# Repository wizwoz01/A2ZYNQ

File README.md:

# A2ZYNQ

**One Apple II slot, seven peripheral cards, running on a Smart Zynq SP.**

A2ZYNQ is my port of the [A2FPGA](https://github.com/a2fpga/a2fpga_core)
Multicard core to the **Smart Zynq SP**, a small Xilinx Zynq-7020 board with
a dual-core ARM, DDR3, HDMI, Ethernet and an SD card slot. A hand-wired proto
card sits in an Apple II slot and connects the Apple bus to the Zynq with a
pair of ribbon cables. The FPGA side runs the A2FPGA core (the same one the
A2N20v2 card uses) and answers for every empty slot in the machine. The ARM
side runs Linux and a small service program, `a2hostd`, that serves disk
images from the SD card, does the networking and runs the boot menu.

The end result: I boot my **Apple IIe** (plain NMOS 6502, 64K, 40
columns) into a disk menu, pick a game from a folder on an SD card, swap disks
with a button on the board, play Total Replay off a 32 MB hard disk, hear the
Mockingboard over HDMI, put the IIe on my home network, and drag disk images
onto it from my PC over FTP. One card does all of it.

```
 Apple IIe slot                          Smart Zynq SP
+--------------------+   2x 40-pin    +-----------------------------------------+
|  proto card        |   ribbons      |  PL (FPGA)                PS (ARM)      |
|  5x SN74LVC245A    |===============>|  A2FPGA core      SPI     Linux         |
|  6x NPN open-coll. |<===============|  - Disk II        over    a2hostd       |
|  /RES sense        |   + ground     |  - ProDOS HDD     AXI <=> - disk images |
+--------------------+   bundle       |  - SSC, Uthernet          - disk menu   |
                                      |  - Mockingboard           - FTP, telnet |
                                      |  - SuperSprite            - SSC bridge  |
                                      |  - HDMI video/audio       - Ethernet    |
                                      +-----------------------------------------+
                                           |HDMI          |SD card   |Ethernet
```

## See it running

All of these are straight HDMI captures from the board on my IIe. The two
GIFs run at double speed. (The row of numbers along the top is the debug
line; DIP switch 4 hides it.)

**The disk menu follows the card.** Same card, moved through slots 1 to 7.
In slots 1-3 the menu says `SLOT n MENU` and the Disk II answers in slot 6;
in slots 4-7 it becomes that slot's own `DISK MENU`.

**Booting a game from the menu.** Arrow down to Oregon Trail, `RETURN`, and
the IIe boots it off the image on the SD card.

**The card test disk.** ProDOS boots, then the test program
([tests/cardtest](tests/cardtest)) goes through every virtual card in
slots 2-7, writes an 8 KB file back to the floppy, reads it back, and ends
with `0 FAILED`. This one is a video with sound, so you can hear the
Mockingboard and SuperSprite test tones come out of the HDMI. Turn the sound up.

https://github.com/user-attachments/assets/9a4790e4-1fdd-43f0-96c2-07918a6907ac

## Why I built this

I wanted an A2FPGA for my IIe, and I already had a Smart Zynq SP on my bench.
The A2N20v2-Enhanced design pairs a Gowin FPGA with a BL616 microcontroller
that serves disks, runs the menu and bridges the network. The Zynq has both
halves on one chip: a decent FPGA, and ARM cores that can run real Linux. So
instead of building another card, I ported the Enhanced design over. The FPGA
logic stays the A2FPGA core, and the BL616's job moves to a Linux program
that speaks the same SPI protocol the BL616 did.

It turned into a much longer project than I expected. The core had to come
off Gowin primitives and onto Xilinx ones, the SDRAM had to become Zynq DDR,
and the Apple bus turned out to be a lot less forgiving than the datasheets
make it look. Along the way I found and fixed a stack of things: an SPI bit
race, a Disk II write path that stored every nibble twice, a hard disk read
that could return stale data, a video shadow that painted neighbour bytes, and
one level translator chip that simply can't do this job (more on that below).
It all works now on my IIe, and the card test disk in this repo passes every
slot.

## What the card provides

With the card in slot 1 (how I run it):

| Slot | Card | What you get |
|------|------|--------------|
| 1 | *(the physical card)* | nothing virtual here, the IIe powers up to BASIC |
| 2 | Super Serial Card | a 6551 serial port, bridged to **TCP port 6551** on the board, so the Apple's serial port shows up on your network |
| 3 | Uthernet II (W5100) | Ethernet for IP65 programs; Apple frames go straight out the board's Ethernet port, and the Apple gets its own address from your router |
| 4 | Mockingboard | two AY-3-8910 sound chips + 6522 VIAs, stereo over HDMI |
| 5 | ProDOS hard disk | two drives up to 32 MB each (`hdd1.hdv`, `hdd2.po`), bootable with `PR#5` |
| 6 | Disk II + disk menu | two 5.25" drives fed from disk images on the SD card, with a boot menu, read **and** write |
| 7 | SuperSprite | TMS9918A video chip with sprites, mixed over the Apple picture on HDMI, plus an AY sound chip |

The Disk II follows the card: put the card in slot 6 and the Disk II answers
in slot 6 and boots at power-up, the hard disk moves to slot 5. Slots 2, 3, 4
and 7 never move. The full table is in the
[board README](boards/a2n20v2-SmartZynq/README.md#slot-map).

Plus:

- **HDMI out** with the Apple picture regenerated (text, lores, hires; the
  core also does 80 columns and double hires, which I can't test without an
  80-column card), with the Apple speaker, Mockingboard and SuperSprite sound
  all on the HDMI audio.
- **A disk menu that runs on the Apple itself.** Folders, arrow keys,
  jump by first letter, `RETURN` boots, `TAB` puts a disk in drive 2, `ESC`
  drops you at BASIC. It remembers the last disk you booted.
- **Disk swapping with board buttons.** `KEY1` on the Smart Zynq puts the next
  disk of a set into drive 1 (`ultima31.dsk` -> `ultima32.dsk`), `KEY2` the
  previous one. A line under the Apple picture on HDMI tells you what's in
  the drive. No keyboard hotkey, nothing a game can trip over.
- **Writes are saved.** DOS 3.3 `SAVE`, ProDOS files, game saves: changed
  tracks are written back into the image on the SD card.
- **FTP server** on the board, so copying games over is drag and drop from
  Windows Explorer, FileZilla or `curl`.
- **Telnet console** with `status`, `rescan` and an FPGA dump command.
- **A card test disk** ([tests/cardtest](tests/cardtest)) that exercises
  every virtual card from the Apple side and writes a log back to the disk.

## Status

This is a working hobby build, not a product. What I've tested on my own
unenhanced IIe:

| | |
|--|--|
| Disk II boot, menu, folders, ESC, drive 2 | works |
| Floppy writes (DOS 3.3 and ProDOS) | works, verified with the card test (0 failed) |
| Multi-disk swap with KEY1/KEY2 | works |
| ProDOS hard disk read/write, Total Replay | works |
| Mockingboard, SuperSprite | works (card test tones and green box) |
| Uthernet II with IP65 (DHCP, DATE65, HFS65 web server) | works |
| Super Serial Card registers | works (card test) |
| SSC over the network (TCP 6551) | works in simulation, real-Apple test still on my list |
| Apple IIgs, enhanced IIe, II+ | not tested. The IIgs signals (M2SEL, M2B0) are wired on the card, but I've never tried it. IIgs mode is off by default because DIP switch 4 hides the HDMI debug numbers instead (one setting in `top.sv` swaps it back) |
| Powering the board from the Apple's +5V | not done yet, see [the power notes](boards/a2n20v2-SmartZynq/docs/power.md) first |
| The rev 1.0 PCB | ordered, waiting on the boards; see [Work in progress](#work-in-progress) |

Known limits on an unenhanced IIe (these are the machine, not the card):
anything built for the 65C02 (ProDOS 8 2.x, Contiki, the C versions of the
IP65 apps) locks up, and 80-column programs show every second character
without an 80-column card.

The open items are in [boards/a2n20v2-SmartZynq/TODO.md](boards/a2n20v2-SmartZynq/TODO.md).

## Work in progress

The firmware, the gateware and the hand-wired card all work today. The
hardware is where most of the open work is, so here's where things stand
and what I'm planning next.

### The PCB (rev 1.0, waiting on boards)

The red proto card works, but it's an evening of point-to-point wiring and
two ribbon cables hanging out of the Apple. So I laid out a real card:
[hardware/pcb](hardware/pcb). Same circuit, same five SN74LVC245A, on an
Apple II card outline (tebl's compact prototyping card), and the Smart Zynq
plugs straight onto it with its HDMI and Ethernet facing the back of the
Apple. No ribbons, no hand wiring.

Where it's at:

- [x] Layout done, KiCad DRC clean, every pad checked against the netlist
      CSVs in [hardware/](hardware/).
- [x] Gerbers, BOM and an assembly sheet in [hardware/pcb](hardware/pcb).
- [x] Boards ordered from the fab.
- [ ] **Waiting on delivery.** Nothing below this line has happened yet.
- [ ] Assemble the first card, do the meter checks from the PCB README
      before it goes anywhere near the IIe.
- [ ] Bring-up in the Apple: card test disk, Disk II boot, hard disk,
      Mockingboard, Uthernet, all the things the proto card already passes.
- [ ] Check the fit: header stack height, standoffs, clearance between the
      Smart Zynq's through-hole pins and the transistors underneath, and
      whether the card clears its neighbours in the slots.
- [ ] Fix whatever rev 1.0 gets wrong and post a rev 1.1 with photos.

**Until I've built one and it passes, treat rev 1.0 as untested.** If you
want to build something right now, build the proto card; the wiring notes
are complete and that's the version I've been running for weeks.

### Other things I'm working toward

- **Powering the Smart Zynq from the Apple.** The PCB has an optional
  Schottky diode and jumper (D1, JP1) to feed the board from the Apple's
  +5V. It ships open and stays that way until I've measured the current
  draw on USB and tried it on the bench. Notes in
  [power.md](boards/a2n20v2-SmartZynq/docs/power.md).
- **SSC network bridge on the real Apple.** It passes in simulation; the
  real IIe test is next on my list.
- **Other machines.** Enhanced IIe, II+, and the IIgs (the IIgs signals are
  already on the card). I only own an unenhanced IIe, so reports are
  welcome.
- **A prebuilt release** (bitstream, `a2hostd`, and maybe a ready SD
  image) so you don't need Vivado to try it.
- **A small web page on the board** for uploading disks and changing
  settings, instead of FTP and editing `settings.ini`.
- **`.woz` image support** for copy-protected originals.
- **Locking down the network side.** FTP, telnet and the serial bridge have
  no passwords right now. Fine on my home network, not fine anywhere else.
  Don't put the board on a network you don't trust yet.
- **Recovering a crashed 6502** from the board, which needs a closer look at
  the /RES and /INH stages.

The full list with the details is in
[TODO.md](boards/a2n20v2-SmartZynq/TODO.md). If you build one, I'd love to
hear how it went, especially on a machine I haven't tried.

## What you need

- An Apple II with a free slot. Mine is a IIe.
- A **Smart Zynq SP** board (XC7Z020-1CLG484) and a USB-C cable/charger for it.
- The **red proto card**, hand-wired per [hardware/RED_PROTO_CARD_WIRING.md](hardware/RED_PROTO_CARD_WIRING.md):
  five SN74LVC245A, seven 2N3904s, a few resistors, two 2x20 headers and two
  40-pin ribbon cables. Parts list in [hardware/BOM.csv](hardware/BOM.csv).
  **Use real SN74LVC245A for the data bus.** Auto-direction translators
  (TXB0108, TXS0108E) do not work, I tried both.
  (Or the [PCB version](hardware/pcb) once I've confirmed it works, see
  [Work in progress](#work-in-progress).)
- A microSD card (4 GB or bigger) for Linux and your disk images.
- An HDMI monitor, and an Ethernet cable if you want FTP and networking.
- To build from source: a Linux PC with **Vivado 2024.2** (the free
  Standard edition covers the XC7Z020) and an ARM cross compiler.

## Getting started

1. **Build or grab the bitstream.** [docs/BUILDING.md](docs/BUILDING.md)
   walks through it: download the Xillinux kit into `third_party/`, run one
   Vivado script, wait half an hour.
2. **Make the SD card.** [docs/INSTALLING.md](docs/INSTALLING.md) covers
   writing Xillinux, putting the bitstream, device tree and `a2hostd` on it,
   and updating a running board later over the network.
3. **Wire the proto card**, check it with a meter before anything goes near
   the Apple, and plug it in with everything powered off.
4. **Power up**: board first (USB-C), wait about 40 seconds, then the Apple.
5. **Use it**: [docs/USER_GUIDE.md](docs/USER_GUIDE.md) explains every card
   with examples you can type in.

## Repository layout

This follows the same layout as `a2fpga_core`, so anyone who knows the
upstream tree will find their way around.

```
A2ZYNQ/
  README.md            you are here
  LICENSE              layered license (MIT + GPL parts), same terms as A2FPGA
  LICENSES/            full GPL-2.0 and GPL-3.0 texts
  hdl/                 the A2FPGA core, with my fixes (disk, hdd, video, ssc bridge...)
  boards/
    a2n20v2-SmartZynq/ everything specific to the Smart Zynq SP
      README.md        the board guide: slots, menu, images, FTP, troubleshooting
      TODO.md          what's left
      hdl/             the a2n20v2-Enhanced top level and SPI connector, ported
      rtl/             Smart Zynq wrapper: board top, bus PHY, clocking, DDR, SPI master
      vivado/          build.tcl, rebuild.tcl, sources.tcl, constraints, BD patch
      device_tree/     merged Xillinux device tree with the A2 UIO node
      src/a2hostd/     the Linux service (C++14): disks, menu, network, SSC bridge
      src/systemd/     a2hostd.service
      tools/           SD card writer, a2hostd cross build, device tree merge
      docs/            how the Zynq side works: SPI map, storage, power, lessons
  docs/
    USER_GUIDE.md      how to use every card, with examples
    BUILDING.md        building the bitstream and a2hostd
    INSTALLING.md      SD card, first boot, updating
    core/              A2FPGA core documentation (from upstream, with my notes)
    images/            HDMI captures used in this README
  hardware/            proto card wiring, BOM, pin maps, schematic (PDF)
    pcb/               the card as a PCB: KiCad board, Gerbers, BOM (rev 1.0, untested)
  tests/
    bus_timing/        xsim testbenches for the bus, Disk II, HDD, menu, SSC bridge...
    cardtest/          Apple II test program for slots 2-7 (cc65)
    menu6502/          runs the disk menu code on a 6502 emulator
  tools/               serial console and file transfer helpers, ProDOS disk builder
  third_party/         where the Xillinux kit goes (not included, see its README)
```

## How it differs from a2n20v2-Enhanced

If you know the upstream board, here's the short version of what changed:

- **BL616 -> Linux.** `a2hostd` on the Zynq ARM takes over everything the
  BL616 firmware did. It talks to the FPGA with the same SPI protocol, through
  a small AXI SPI master in the PL that Linux drives through UIO, so the
  core's `bl616_spi_connector` barely had to change.
- **SDRAM -> DDR3.** The core's memory clients share an arbiter that is
  bridged across clock domains into the Zynq's HP2 AXI port, using a reserved
  8 MiB window at `0x1E000000`.
- **Gowin -> Xilinx.** Clocking (MMCM), HDMI TMDS serializers (OSERDESE2),
  tri-states and a few memories were rewritten or wrapped for Vivado.
- **CPLD -> five 245s.** The original card captures the bus with a CPLD; the
  proto card uses five SN74LVC245A and puts all the capture and timing logic
  in the FPGA, with drive timing you can tune from Linux.
- **Storage paths I added.** Floppy saves read the track straight back out of
  the drive's nibble memory, and hard disk blocks go straight to and from the
  controller's sector buffer. The upstream SDRAM round trip wasn't reliable on
  this port (the card test caught it).
- **Extras:** the 6502 disk menu with folders and ESC, the Disk II following
  the card's slot, board-button disk swaps with an HDMI notice line, the SSC
  network bridge, FTP/telnet on the board, and BRAM shadows for text and
  hires video.

## Things I learned the hard way

- **Auto-direction level shifters don't belong on the Apple data bus.**
  TXB0108 and TXS0108E both read isolated 0 bits as 1 (things like `$BD`
  became `$FF` 40-85% of the time) and no amount of FPGA timing fixed it. An
  SN74LVC245A with the FPGA driving DIR and OE# fixed it on the first boot.
- **6502 dummy reads are real bus cycles.** `STA abs,X`, `STA (zp),Y` and
  Applesoft's `POKE` all read the address before they write it. Any register
  with a read side effect (auto-increment, clear-on-read) gets hit twice. The
  Uthernet II DHCP bug I chased was exactly this.
- **Act at the end of the bus cycle.** The card sees selects at the start of
  PHI0, so anything that "fires on select" can fire twice per access. That's
  what made the Disk II write every nibble twice.
- **Don't restart the host service under a running Apple.** If `a2hostd`
  drops out, the card stops answering and the 6502 crashes. Restart it only
  with the Apple switched off.

The long version, with the measurements, is in
[boards/a2n20v2-SmartZynq/docs/lessons-learned.md](boards/a2n20v2-SmartZynq/docs/lessons-learned.md).

## Documentation

| Document | What's in it |
|----------|--------------|
| [boards/a2n20v2-SmartZynq/README.md](boards/a2n20v2-SmartZynq/README.md) | The board guide: slot map, disk images, first boot, menu, FTP, network, troubleshooting |
| [docs/USER_GUIDE.md](docs/USER_GUIDE.md) | Every card explained with examples (BASIC listings, PC commands) |
| [docs/BUILDING.md](docs/BUILDING.md) | Building the bitstream and `a2hostd`, running the tests |
| [docs/INSTALLING.md](docs/INSTALLING.md) | SD card, first boot, updating the board |
| [boards/a2n20v2-SmartZynq/docs/](boards/a2n20v2-SmartZynq/docs/) | How the Zynq port works inside: SPI host interface, storage, SSC bridge, power, lessons learned |
| [hardware/RED_PROTO_CARD_WIRING.md](hardware/RED_PROTO_CARD_WIRING.md) | Wiring the proto card, the electrical rules, bring-up checks |
| [hardware/pcb/README.md](hardware/pcb/README.md) | The PCB version: ordering, how the Smart Zynq sits on it, assembly and meter checks |
| [docs/core/](docs/core/) | The A2FPGA core docs: architecture, bus interface, memory, video, audio, peripheral cards |

## Credits

This project stands on other people's work, and I want to be clear about that.

- **[A2FPGA](https://github.com/a2fpga/a2fpga_core)** by Ed Anuff and the
  A2FPGA contributors. The core, the virtual cards, the video pipeline and the
  a2n20v2-Enhanced design I ported all come from there. My port started from
  upstream commit `f97dc342`.
- The open cores inside A2FPGA: the 6522 VIA by Gideon Zweijtzer
  (1541ultimate), the IIR filter by Sorgelig (MiSTer), the F18A/TMS9918 core,
  the YM2149 (AY-3-8910) and 6551 cores, the TMS5220, and the AppleWin team, whose HDD
  firmware and 6-and-2 GCR code live on in the hard disk ROM and in `a2hostd`.
- **[Xillybus](https://xillybus.com)** for Xillinux and the Smart Zynq SP
  demo bundle that the build starts from.
- **[Total Replay](https://github.com/a2-4am/4cade)** by 4am and qkumba, which
  is what I keep on hard disk 1.
- **[IP65](https://github.com/cc65/ip65)** for the Uthernet test disk.
- **[cc65](https://cc65.github.io)** for building the card test, and
  **[py65](https://github.com/mnaberez/py65)** for testing the menu code
  without an Apple.

## License

Same terms as A2FPGA: MIT for the A2FPGA and A2ZYNQ files, with a few GPL
components that make the bitstream as a whole GPL-3.0. Details in
[LICENSE](LICENSE). The Xillinux kit is Xillybus's and is not included.

Apple, Apple II and ProDOS are trademarks of Apple Inc. This is a hobby
project with no connection to Apple, AMD/Xilinx, Xillybus or the Smart Zynq
maker.

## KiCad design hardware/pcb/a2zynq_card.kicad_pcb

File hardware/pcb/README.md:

# pcb: the A2ZYNQ slot card

This is the red proto card turned into a real PCB. The circuit is exactly the
one in [../RED_PROTO_CARD_WIRING.md](../RED_PROTO_CARD_WIRING.md) and the
`../*.csv` netlists (five SN74LVC245A, Q1-Q7, the 5 V sense divider, SW1),
and the Smart Zynq SP plugs straight onto the card, so there are no ribbon
cables and no hand wiring.

> **Status: rev 1.0, boards ordered, not built yet.** The board passes KiCad's DRC with no
> errors, and I checked every pad against the CSV netlists. The first
> boards have not been through the Apple yet, so treat rev 1.0 as a
> prototype: order the minimum quantity and do the meter checks below before
> it goes near the IIe.

## Order it

Upload **`a2zynq_card_gerbers.zip`** to the fab (JLCPCB, PCBWay, OSH Park...).

| Setting | Value |
|---------|-------|
| Layers | 2 |
| Size | 99.7 x 78.7 mm (68.6 mm above the edge fingers) |
| Thickness | 1.6 mm (the Apple slot wants 1.57 mm / 0.062") |
| Copper | 1 oz |
| Smallest track / gap | 0.25 mm / 0.2 mm |
| Smallest hole | 0.3 mm (vias) |
| Surface finish | ENIG, or "gold fingers" if the fab offers it |
| Edge fingers | bevel (chamfer) the finger edge if offered; it makes insertion kinder to the slot |

The outline and the 50 edge fingers follow tebl's
[Apple ][ Prototyping Card](https://github.com/tebl/Apple2-Prototyping-Card)
(the compact one): same size, same finger position and pitch, so it sits in
the slot exactly like that card.

## How the Smart Zynq sits on it

- The Smart Zynq goes **component side up**, turned so its **HDMI and
  Ethernet face the back panel** of the Apple (the right-hand end of the card,
  looking at the component side with the fingers down). Its USB-C ports face
  the keyboard.
- **JZ1 = Smart Zynq U12** (bank 33, the header on the HDMI side of the
  Smart Zynq). It's the row next to the edge fingers.
- **JZ2 = Smart Zynq U13** (bank 35, the header on the Ethernet side). It's
  the row along the top edge.
- Pin 1 of both is the **square pad at the right-hand end**. Pins 35/36 are
  ground, 37/38 are 3.3 V, 39/40 are the board's 5 V, the same as on the
  Smart Zynq.
- The four M3 holes line up with the Smart Zynq's four corner holes. Use
  standoffs the same height as the header stack (about 11 mm with ordinary
  8.5 mm female headers on the card and the Smart Zynq's pins underneath).

Header and hole positions come from the board maker's dimension drawing
(`Smart_ZYNQ_SP_V1_SIZE_20230502.pdf`): header pins start 23.94 mm from the
board edge, the two pin-1 rows are 48.08 mm apart, holes 87.14 x 45 mm. Which
header is U12 comes from the Smart Zynq schematic and its ball map (bank 33
is the top half of the BGA, next to the HDMI header).

If your Smart Zynq has its header pins on the top side (they point up, for
ribbon cables), you can still use the card: fit **2x20 box headers** in JZ1
and JZ2 and run two short ribbon cables, U12 to JZ1 and U13 to JZ2, pin 1 to
pin 1. The numbering on the card is the same either way.

### Height under the Smart Zynq

Everything on the card except SW1, D1, JP1, R23 and TP1 sits under the
Smart Zynq, so keep it low:

- solder the '245s straight in or use low-profile sockets,
- push the transistors down to about 5 mm above the board,
- C6 and C7 must be **7 mm tall or less** (low-profile electrolytics).

The Smart Zynq's Ethernet jack is through-hole, and its pins come out of the
underside right above Q1-Q6, the same way the HDMI shell legs sit above Q7
and R13-R18. Before tightening the standoffs, put the board on and look along
the gap from the side: nothing on the card should touch the pins.

The Smart Zynq's microSD socket isn't on its top side (it's not on the
maker's top-view drawing), so expect to lift the board off the sockets to
swap cards. I update the card over the network anyway (see the board
README).

## Parts

Full list: [a2zynq_card_bom.csv](a2zynq_card_bom.csv). The "old schematic name"
column ties each part back to the hand-wired card and the PDF schematic
(RBASE1, ROE_IN, CDEC3 and so on).

The resistors use the small **0204 size** (3.6 mm body, 5.08 mm lead
spacing), for example Vishay SFR16S or Yageo MFR-12. The usual 1/4 W
6.3 mm resistors don't fit the footprint. Everything else is ordinary
through-hole.

Differences from the hand-wired card:

- U5 is an **SN74LVC245A** with DIR and OE# from the FPGA, as in the wiring
  notes. The old PDF schematic still shows the TXB0108; ignore that page.
- No separate ground bundle: both headers carry two ground pins each, and
  the card has ground pours on both sides. TP1 is a ground loop for a scope
  clip.
- U13 pin 27 (`pl_ready`) isn't connected to anything, same as before.

## SW1

Left-hand end of the card, next to the fingers, so it's reachable with the
Smart Zynq in place. Positions 1-4 left to right are the same as always:
1 scanlines, 2 Apple speaker on HDMI, 3 Power-on-Reset hold, 4 hide the HDMI
debug numbers (see the board README). Each switch pulls its JZ2 pin
(15-18) to ground.

## The 5 V link (JP1 and D1, optional)

Leave **JP1 open** and the card is "ground only", exactly like the wiring
notes: Apple +5V only feeds the 15k/22k sense divider and the Smart Zynq runs
from USB-C.

To run the Smart Zynq from the Apple's +5V, fit **D1 (1N5822, 3 A Schottky)
first**: it stands upright on the round pad with its band (cathode) at the
top, and the lead from the band goes down to the square pad marked K. Then
put a jumper on JP1. Apple slot pin 25 then goes through JP1 and D1 to the Smart
Zynq's 5 V (U13 pins 39/40) on a 1 mm track around the edge of the card, and
D1 stops USB power from back-feeding the Apple. Read
[docs/power.md](../../boards/a2n20v2-SmartZynq/docs/power.md) before doing
this: check the board's current on USB first, check 4.6 V or more at pin 39
under load, and keep DIP switch 3 ON.

## Before it goes in the Apple

1. Card alone, nothing fitted in the sockets yet: meter Apple finger 25 to
   26. It must not beep.
2. Fit the parts. Card alone again: finger 25 to 26 reads about 37k (the
   sense divider), not a short. Check every edge finger against its
   neighbours.
3. Smart Zynq on the card, card **not** in the Apple, board on USB-C: 3.3 V
   on pin 20 of each '245, and OE# (pin 19) high on all five. Without the
   Apple's 5 V the FPGA keeps the bus switched off, and the 10k pull-ups hold
   OE# high before the bitstream loads.
4. With the A2ZYNQ bitstream running and the card still out of the Apple,
   JZ2 pins 15-18 read 3.3 V with each switch OFF and 0 V with it ON.
5. Everything off. Card in the slot. Board first, then the Apple, and watch
   the `a2hostd` log for the detected slot.

Never plug or unplug the card (or the Smart Zynq) with either side powered.

## Files

| File | What it is |
|------|------------|
| `a2zynq_card_gerbers.zip` | Gerbers + drill files, ready to upload |
| `a2zynq_card.kicad_pcb`, `a2zynq_card.kicad_pro` | the board, opens in KiCad 9 |
| `a2zynq_card_bom.csv` | parts list |
| `top.png`, `bottom.png`, `assembly.pdf` | previews (the bottom one as seen from the back) and an assembly drawing |
| `drc.rpt` | KiCad's DRC report for the board: no errors, nothing unconnected; the warnings are silkscreen overlaps and the three footprints from my own library (JZ1, JZ2 and the edge fingers J1) |

There's no KiCad schematic for this board. The netlist is the `../*.csv`
files, and I checked every pad on the copper against them.

### Changing the board

Open `a2zynq_card.kicad_pro` in KiCad 9 and edit it in the PCB editor. Before
ordering, refill the zones (B) and run the DRC (Inspect > Design Rules
Checker). To make the fab zip the same way as the one here:

```bash
cd hardware/pcb
mkdir -p gerbers
kicad-cli pcb export gerbers --layers F.Cu,B.Cu,F.Mask,B.Mask,F.SilkS,B.SilkS,Edge.Cuts \
    --subtract-soldermask -o gerbers/ a2zynq_card.kicad_pcb
kicad-cli pcb export drill --format excellon --excellon-units mm --excellon-separate-th \
    -o gerbers/ a2zynq_card.kicad_pcb
rm -f a2zynq_card_gerbers.zip
(cd gerbers && zip -q -9 ../a2zynq_card_gerbers.zip *)
```

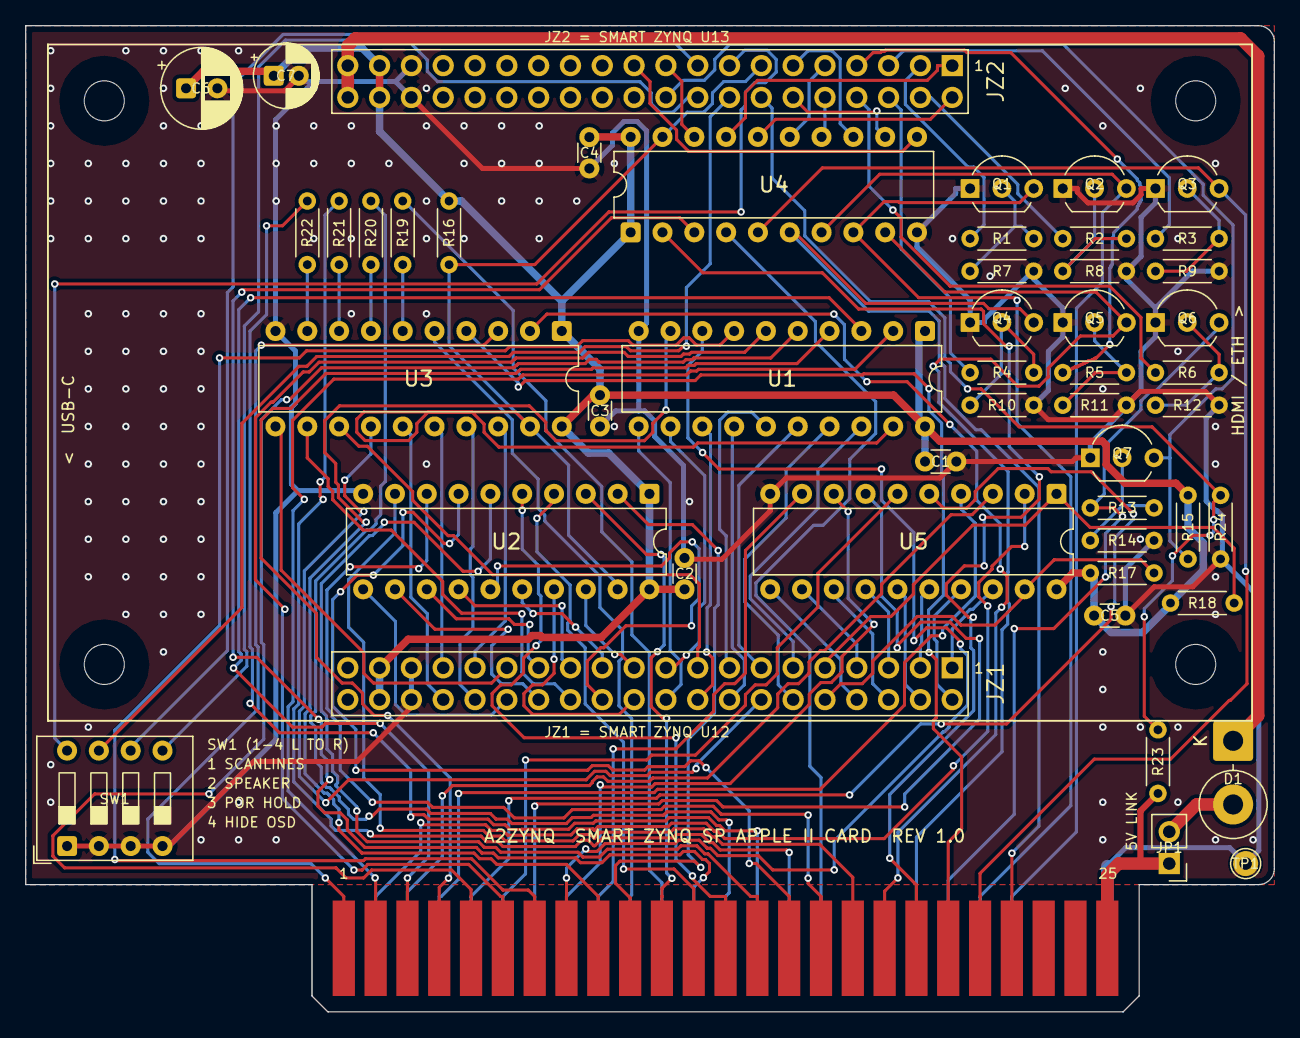
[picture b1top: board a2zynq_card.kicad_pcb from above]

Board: 2 copper layers, 99.7 x 78.7 mm, 54 parts (0 on the bottom side), 112 nets.

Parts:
C1, C2, C3, C4, C5: 100n; C_Disc_D3.0mm_W1.6mm_P2.50mm
C6: 100u; CP_Radial_D6.3mm_P2.50mm
C7: 10u; CP_Radial_D5.0mm_P2.00mm
D1: 1N5822 (option); D_DO-201AD_P5.08mm_Vertical_KathodeUp
J1: Apple II slot; Apple_II_Slot_Edge
JP1: 5V LINK (open); PinHeader_1x02_P2.54mm_Vertical
JZ1: Smart Zynq U12 (bank 33); SmartZynq_2x20_U12
JZ2: Smart Zynq U13 (bank 35); SmartZynq_2x20_U13
MH1, MH2, MH3, MH4: M3; MountingHole_3.2mm_M3
Q1, Q2, Q3, Q4, Q5, Q6, Q7: 2N3904; TO-92_Inline_Wide
R1, R2, R3, R4, R5, R6: 2.2k; R_Axial_DIN0204_L3.6mm_D1.6mm_P5.08mm_Horizontal
R7, R8, R9, R10, R11, R12, R16, R17, R18: 10k; R_Axial_DIN0204_L3.6mm_D1.6mm_P5.08mm_Horizontal
R13, R23: 15k; R_Axial_DIN0204_L3.6mm_D1.6mm_P5.08mm_Horizontal
R14: 100k; R_Axial_DIN0204_L3.6mm_D1.6mm_P5.08mm_Horizontal
R15: 4.7k; R_Axial_DIN0204_L3.6mm_D1.6mm_P5.08mm_Horizontal
R19, R20, R21, R22: 33R; R_Axial_DIN0204_L3.6mm_D1.6mm_P5.08mm_Horizontal
R24: 22k; R_Axial_DIN0204_L3.6mm_D1.6mm_P5.08mm_Horizontal
SW1: DIP x4; SW_DIP_SPSTx04_Slide_9.78x12.34mm_W7.62mm_P2.54mm
TP1: GND; TestPoint_THTPad_D2.0mm_Drill1.0mm
U1, U2, U3, U4, U5: SN74LVC245AN; DIP-20_W7.62mm

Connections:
5V_LINK: D1.2, JP1.2
A0: J1.2, U1.2
A1: J1.3, U1.3
A2: J1.4, U1.4
A2_5V_PRESENT: JZ2.14, R23.2, R24.1
A2_7M: JZ1.26, U3.12
A2_ADDR0: JZ1.11, U1.18
A2_ADDR1: JZ1.12, U1.17
A2_ADDR2: JZ1.13, U1.16
A2_ADDR3: JZ1.15, U1.15
A2_ADDR4: JZ1.16, U1.14
A2_ADDR5: JZ1.18, U1.13
A2_ADDR6: JZ1.19, U1.12
A2_ADDR7: JZ1.20, U1.11
A2_ADDR8: JZ1.21, U2.18
A2_ADDR9: JZ1.22, U2.17
A2_ADDR10: JZ1.23, U2.16
A2_ADDR11: JZ1.24, U2.15
A2_ADDR12: JZ1.25, U2.14
A2_ADDR13: JZ1.27, U2.13
A2_ADDR14: JZ1.28, U2.12
A2_ADDR15: JZ1.30, U2.11
A2_DATA0: JZ1.1, U5.18
A2_DATA1: JZ1.2, U5.17
A2_DATA2: JZ1.3, U5.16
A2_DATA3: JZ1.4, U5.15
A2_DATA4: JZ1.5, U5.14
A2_DATA5: JZ1.6, U5.13
A2_DATA6: JZ1.7, U5.12
A2_DATA7: JZ1.8, U5.11
A2_DATA_DIR: JZ1.9, R18.2, U5.1
A2_DATA_OE_N: JZ1.10, R17.2, U5.19
A2_DEVSEL_N: JZ1.34, U3.15
A2_DMA_ASSERT: JZ2.6, R4.1
A2_DMA_N_SENSE: JZ2.10, U4.14
A2_INH_ASSERT: JZ2.7, R5.1
A2_INH_N_SENSE: JZ2.21, U4.11
A2_IOSEL_N: JZ1.32, U3.17
A2_IOSTRB_N: JZ1.33, U3.16
A2_IRQ_ASSERT: JZ2.3, R1.1
A2_IRQ_N_SENSE: JZ2.12, U4.12
A2_M2B0: JZ2.2, U4.16
A2_M2SEL: JZ2.1, U4.17
A2_NMI_ASSERT: JZ2.4, R2.1
A2_NMI_N_SENSE: JZ2.11, U4.13
A2_PHI0: JZ1.14, U3.14
A2_PHI1: JZ1.17, U3.13
A2_Q3: JZ1.29, U3.11
A2_RDY_ASSERT: JZ2.5, R3.1
A2_RDY_N_SENSE: JZ2.9, U4.15
A2_RESET_ASSERT: JZ2.8, R6.1
A2_RESET_ASSERTED_SENSE: JZ2.20, Q7.3, R15.2
A2_RW: JZ1.31, U3.18
A2_SYNC: JZ2.19, U4.18
A3: J1.5, U1.5
A4: J1.6, U1.6
A5: J1.7, U1.7
A6: J1.8, U1.8
A7: J1.9, U1.9
A8: J1.10, U2.2
A9: J1.11, U2.3
A10: J1.12, U2.4
A11: J1.13, U2.5
A12: J1.14, U2.6
A13: J1.15, U2.7
A14: J1.16, U2.8
A15: J1.17, U2.9
BUS_INPUT_OE_N: JZ2.13, R16.2, U1.19, U2.19, U3.19, U4.19
CARD_5V: J1.25, JP1.1, R23.1
CLK7M: J1.36, R21.1
CLK7M_R: R21.2, U3.8
D0: J1.49, U5.2
D1: J1.48, U5.3
D2: J1.47, U5.4
D3: J1.46, U5.5
D4: J1.45, U5.6
D5: J1.44, U5.7
D6: J1.43, U5.8
D7: J1.42, U5.9
DEVSEL_N: J1.41, U3.5
DIP_SW1: JZ2.15, SW1.8
DIP_SW2: JZ2.16, SW1.7
DIP_SW3: JZ2.17, SW1.6
DIP_SW4: JZ2.18, SW1.5
DMA_N: J1.22, Q4.3, U4.6
GND: C1.2, C2.2, C3.2, C4.2, C5.2, C6.2, C7.2, J1.26, JZ1.35, JZ1.36, JZ2.35, JZ2.36, Q1.1, Q2.1, Q3.1, Q4.1, Q5.1, Q6.1, Q7.1, R7.2, R8.2, R9.2, R10.2, R11.2, R12.2, R14.2, R24.2, SW1.1, SW1.2, SW1.3, SW1.4, TP1.1, U1.10, U2.10, U3.10, U4.10, U5.10
INH_N: J1.32, Q5.3, U4.9
IOSEL_N: J1.1, U3.3
IOSTRB_N: J1.20, U3.4
IRQ_N: J1.30, Q1.3, U4.8
M2B0: J1.35, U4.4
M2SEL: J1.39, U4.3
NMI_N: J1.29, Q2.3, U4.7
PHI0: J1.40, R19.1
PHI0_R: R19.2, U3.6
PHI1: J1.38, R20.1
PHI1_R: R20.2, U3.7
Q1_BASE: Q1.2, R1.2, R7.1
Q2_BASE: Q2.2, R2.2, R8.1
Q3: J1.37, R22.1
Q3_BASE: Q3.2, R3.2, R9.1
Q3_R: R22.2, U3.9
Q4_BASE: Q4.2, R4.2, R10.1
Q5_BASE: Q5.2, R5.2, R11.1
Q6_BASE: Q6.2, R6.2, R12.1
Q7_BASE: Q7.2, R13.2, R14.1
RDY_N: J1.21, Q3.3, U4.5
RES_N: J1.31, Q6.3, R13.1
RW: J1.18, U3.2
SYNC: J1.19, U4.2
VCC3V3: C1.1, C2.1, C3.1, C4.1, C5.1, C6.1, C7.1, JZ1.37, JZ1.38, JZ2.37, JZ2.38, R15.1, R16.1, R17.1, R18.1, U1.1, U1.20, U2.1, U2.20, U3.1, U3.20, U4.1, U4.20, U5.20
ZYNQ_5V: D1.1, JZ2.39, JZ2.40

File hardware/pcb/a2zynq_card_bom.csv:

References,Qty,Value,Footprint,Old schematic name,Notes
C1 C2 C3 C4 C5,5,100 nF,C_Disc_D3.0mm_W1.6mm_P2.50mm,CDEC1 CDEC2 CDEC3 CDEC4 CDEC5,"ceramic, 2.5 mm lead spacing"
C6,1,100 uF 10 V,CP_Radial_D6.3mm_P2.50mm,CBULK1,"electrolytic, 6.3 mm, 2.5 mm spacing, 7 mm tall or less (sits under the Smart Zynq)"
C7,1,10 uF 10 V,CP_Radial_D5.0mm_P2.00mm,CBULK2,"electrolytic, 5 mm, 2.0 mm spacing, 7 mm tall or less"
D1,1,1N5822,D_DO-201AD_P5.08mm_Vertical_KathodeUp,,"OPTIONAL, only with JP1: 3 A Schottky, mounted upright, band (cathode) on the top lead"
JP1,1,1x2 pin header + jumper,PinHeader_1x02_P2.54mm_Vertical,,"OPTIONAL 5V link, leave OPEN unless D1 is fitted (docs/power.md)"
JZ1,1,2x20 female header 2.54 mm,SmartZynq_2x20_U12,,"Smart Zynq U12 (bank 33); standard 8.5 mm socket for mounting the board on the card, or a 2x20 box header for a ribbon cable"
JZ2,1,2x20 female header 2.54 mm,SmartZynq_2x20_U13,,"Smart Zynq U13 (bank 35); standard 8.5 mm socket for mounting the board on the card, or a 2x20 box header for a ribbon cable"
Q1 Q2 Q3 Q4 Q5 Q6 Q7,7,2N3904,TO-92_Inline_Wide,,"TO-92, E-B-C pinout (PN2222A also works if it is E-B-C)"
R1 R2 R3 R4 R5 R6,6,2.2k,R_Axial_DIN0204_L3.6mm_D1.6mm_P5.08mm_Horizontal,RBASE1 RBASE2 RBASE3 RBASE4 RBASE5 RBASE6,"0204 size axial (3.6 mm body), 5.08 mm lead spacing, 1/6 W or more"
R7 R8 R9 R10 R11 R12 R16 R17 R18,9,10k,R_Axial_DIN0204_L3.6mm_D1.6mm_P5.08mm_Horizontal,RBE1 RBE2 RBE3 RBE4 RBE5 RBE6 ROE_IN ROE_DATA RDIR_DATA,"0204 size axial (3.6 mm body), 5.08 mm lead spacing, 1/6 W or more"
R13 R23,2,15k,R_Axial_DIN0204_L3.6mm_D1.6mm_P5.08mm_Horizontal,RRESET_BASE RSENSE_TOP,"0204 size axial (3.6 mm body), 5.08 mm lead spacing, 1/6 W or more"
R14,1,100k,R_Axial_DIN0204_L3.6mm_D1.6mm_P5.08mm_Horizontal,RRESET_BE,"0204 size axial (3.6 mm body), 5.08 mm lead spacing, 1/6 W or more"
R15,1,4.7k,R_Axial_DIN0204_L3.6mm_D1.6mm_P5.08mm_Horizontal,RRESET_COL,"0204 size axial (3.6 mm body), 5.08 mm lead spacing, 1/6 W or more"
R19 R20 R21 R22,4,33R,R_Axial_DIN0204_L3.6mm_D1.6mm_P5.08mm_Horizontal,RSER1 (PHI0) RSER2 (PHI1) RSER3 (7M) RSER4 (Q3),"0204 size axial (3.6 mm body), 5.08 mm lead spacing, 1/6 W or more"
R24,1,22k,R_Axial_DIN0204_L3.6mm_D1.6mm_P5.08mm_Horizontal,RSENSE_BOTTOM,"0204 size axial (3.6 mm body), 5.08 mm lead spacing, 1/6 W or more"
SW1,1,4-position DIP switch,SW_DIP_SPSTx04_Slide_9.78x12.34mm_W7.62mm_P2.54mm,,"slide type, 2.54 mm pitch, 7.62 mm row spacing"
TP1,1,test point,TestPoint_THTPad_D2.0mm_Drill1.0mm,,optional ground loop for a scope clip
U1 U2 U3 U4 U5,5,SN74LVC245AN,DIP-20_W7.62mm,SN74LVC245A SN74LVC245A SN74LVC245A SN74LVC245A SN74LVC245A,"PDIP-20. Exactly this part: not HC/HCT/LS, never TXB0108/TXS0108E. A socket is fine."
MH1-MH4,4,M3 standoff + screw,MountingHole_3.2mm_M3,,standoff length = header stack height (about 11 mm with 8.5 mm sockets)
